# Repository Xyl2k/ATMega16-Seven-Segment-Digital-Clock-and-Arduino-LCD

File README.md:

# ATMega16-Seven-Segment-Digital-Clock-and-Arduino-LCD

Original schematic: http://www.avr-tutorials.com/projects/atmega16-based-digital-clock

edit: do not build for the moment, rookie mistake on lcd/arduino routing, i used A2,A3,A4,A5 pins instead of D2,D3,D4,D5...

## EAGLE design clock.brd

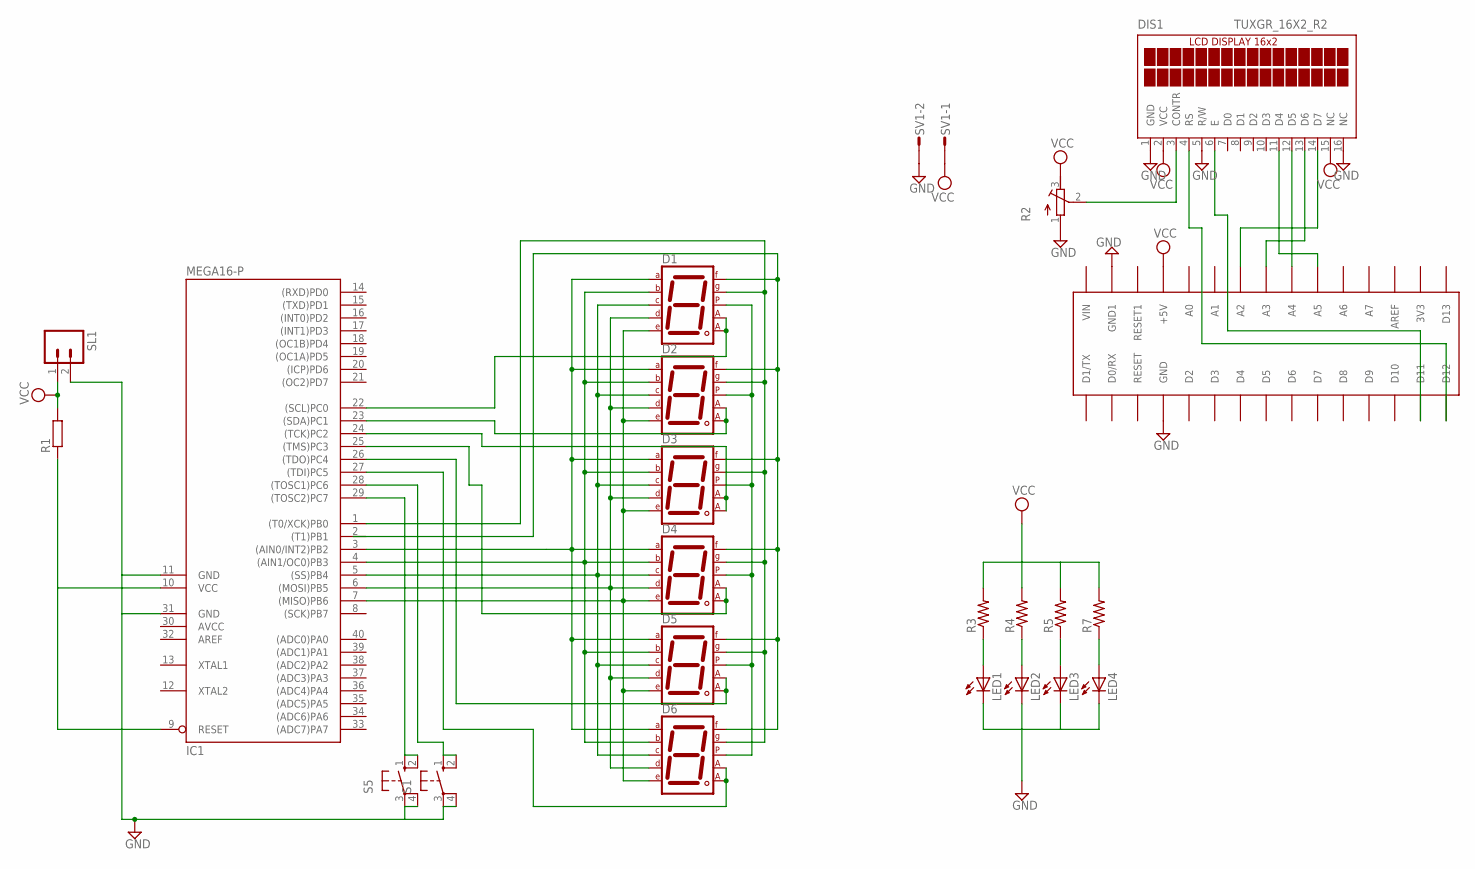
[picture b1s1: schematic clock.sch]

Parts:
D1, D2, D3, D4, D5, D6: 7SEG-CA; 7SEG-13
DIS1: TUXGR_16X2_R2
IC1: MEGA16-P; DIL40
LED1, LED2, LED3, LED4: LED_ESML0603; LED_SML0603
R1: R-EU_0204/7; 0204/7
R2: R-TRIMM3339P; RTRIM3339P
R3, R4, R5, R7: R-US_R0603; R0603
S1, S5: 10-XX; B3F-10XX
SL1: M02; 02P
SV1: L02P
U$1: ARDUINONANO; PDIP-32

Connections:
AVCC: IC1.30 (AVCC)
GND: DIS1.1 (GND), DIS1.5 (R/W), DIS1.16 (NC), IC1.11 (GND), IC1.31 (GND), LED1.C, LED2.C, LED3.C, LED4.C, R2.1 (E), S1.3, S1.4 (P1), S5.3, S5.4 (P1), SL1.2, SV1.2, U$1.GND, U$1.GND1
unnamed: D1.7 (A), D2.7 (A), D3.7 (A), D4.7 (A), D5.7 (A), D6.7 (A), IC1.3 ((AIN0/INT2)PB2)
unnamed: D1.6 (B), D2.6 (B), D3.6 (B), D4.6 (B), D5.6 (B), D6.6 (B), IC1.4 ((AIN1/OC0)PB3)
unnamed: D1.4 (C), D2.4 (C), D3.4 (C), D4.4 (C), D5.4 (C), D6.4 (C), IC1.5 ((SS)PB4)
unnamed: D1.2 (D), D2.2 (D), D3.2 (D), D4.2 (D), D5.2 (D), D6.2 (D), IC1.6 ((MOSI)PB5)
unnamed: D1.1 (E), D2.1 (E), D3.1 (E), D4.1 (E), D5.1 (E), D6.1 (E), IC1.7 ((MISO)PB6)
unnamed: D1.9 (F), D2.9 (F), D3.9 (F), D4.9 (F), D5.9 (F), D6.9 (F)
unnamed: D1.10 (G), D2.10 (G), D3.10 (G), D4.10 (G), D5.10 (G), D6.10 (G), IC1.1 ((T0/XCK)PB0)
unnamed: D1.5 (DP), D2.5 (DP), D3.5 (DP), D4.5 (DP), D5.5 (DP), D6.5 (DP)
unnamed: D6.3 (CA1), D6.8 (CA2), IC1.27 ((TDI)PC5)
unnamed: D5.3 (CA1), D5.8 (CA2), IC1.26 ((TDO)PC4)
unnamed: D4.3 (CA1), D4.8 (CA2), IC1.25 ((TMS)PC3)
unnamed: D3.3 (CA1), D3.8 (CA2), IC1.24 ((TCK)PC2)
unnamed: D2.3 (CA1), D2.8 (CA2), IC1.23 ((SDA)PC1)
unnamed: D1.3 (CA1), D1.8 (CA2), IC1.22 ((SCL)PC0)
unnamed: LED1.A, R3.1
unnamed: IC1.28 ((TOSC1)PC6), S1.1 (S), S1.2 (S1)
unnamed: IC1.29 ((TOSC2)PC7), S5.1 (S), S5.2 (S1)
unnamed: LED2.A, R4.1
unnamed: IC1.9 (RESET), IC1.10 (VCC), R1.1
unnamed: DIS1.4 (RS), U$1.D12
unnamed: DIS1.6 (E), U$1.D11
unnamed: DIS1.3 (CONTR), R2.2 (S)
unnamed: DIS1.14 (D7), U$1.A2
unnamed: DIS1.13 (D6), U$1.A3
unnamed: DIS1.12 (D5), U$1.A4
unnamed: DIS1.11 (D4), U$1.A5
unnamed: LED3.A, R5.1
unnamed: LED4.A, R7.1
VCC: DIS1.2 (VCC), DIS1.15 (NC), R1.2, R2.3 (A), R3.2, R4.2, R5.2, R7.2, SL1.1, SV1.1, U$1.+5V

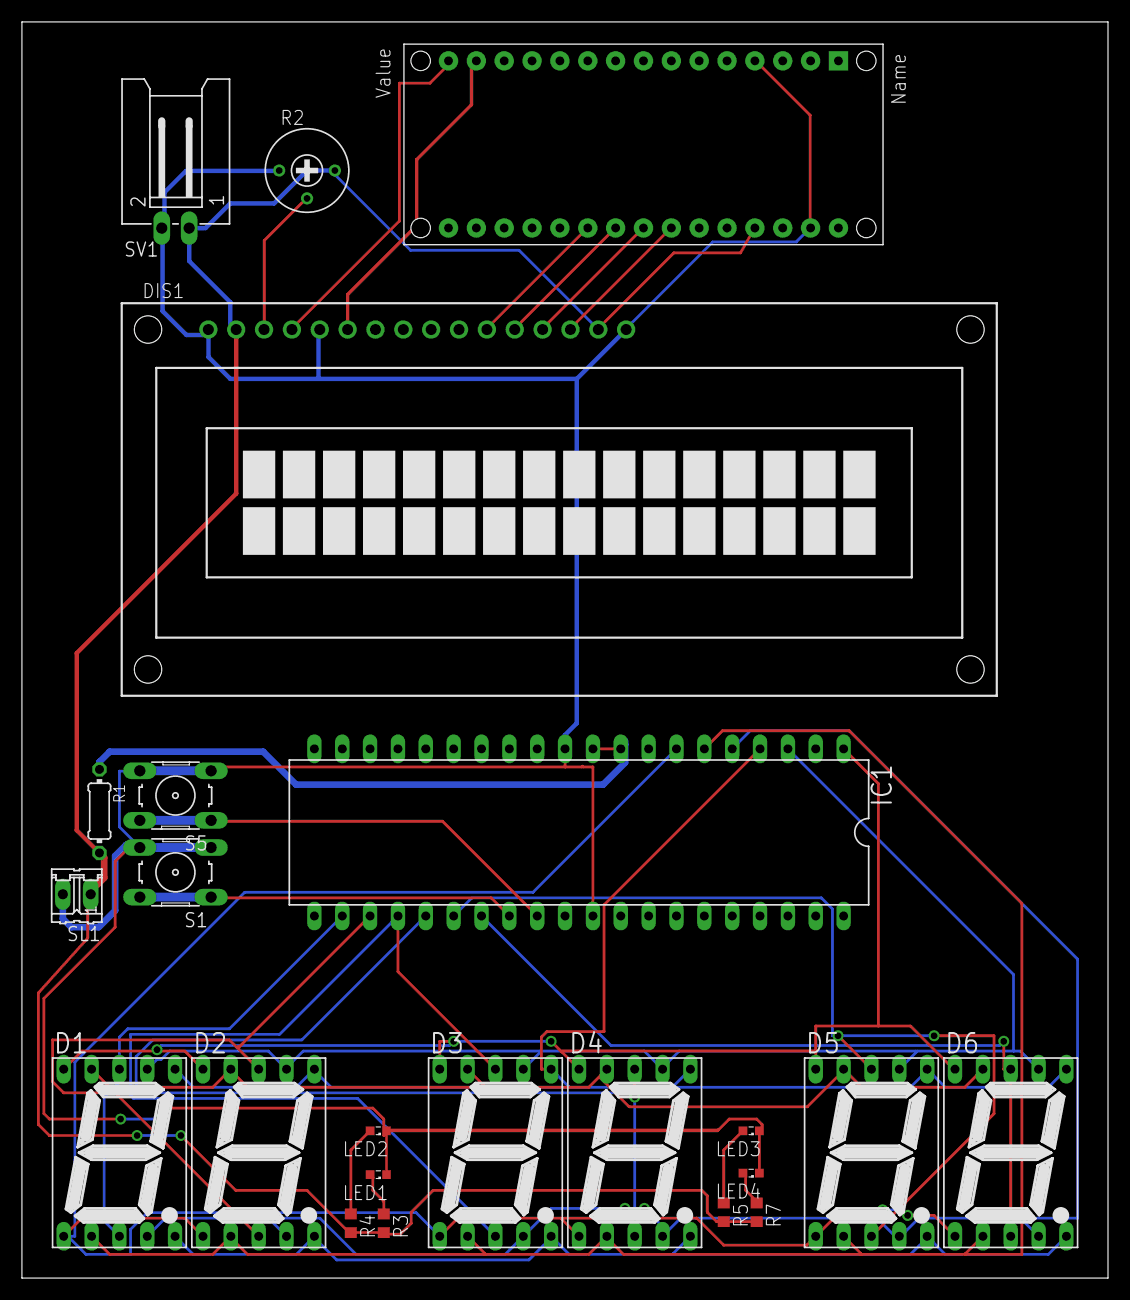
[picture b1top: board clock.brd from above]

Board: 2 copper layers, 99.0 x 114.5 mm, 23 parts (0 on the bottom side), 30 nets.

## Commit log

2015-01-28 :space_invader: Added .gitattributes & .gitignore files
2015-01-28 1.0
    1.0
2015-02-04 1.1
    added smd leds and bugfixed a route.
